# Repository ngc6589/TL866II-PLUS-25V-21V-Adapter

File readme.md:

# TL866II PLUS 25V/21V アダプター

## 概要
当アダプタは XGecu TL866II PLUS プログラマにて 2716/2732 UV-EPROM 書き込みのための 25V/21V を供給するサポートアダプターです。TL866II PLUS の書き込み電圧 18V を検出すると ROM の VPP ピンに 25V/21V を供給します。25V/21V の電圧は  9～12V の ACアダプタから供給された電圧を昇圧ICで 25V/21V にします。

基板とスライドスイッチは https://www.em9system.com/?p=965 にて頒布いたします。

## 部品表
本来は部品の種類別にソートするものですが、購入先別に分けて記載しています。

|部品番号|部品名|URL|数量|備考|
|----|----|----|----|----|
|U1|DCDCコンバーター制御用IC NJM2360AD|https://akizukidenshi.com/catalog/g/gI-12365/|1|MC34063A も使えます|
|U1|丸ピンICソケット ( 8P)|https://akizukidenshi.com/catalog/g/gP-00035/|1|
|Q1|トランジスタ 2SA733L-K-T92-K 60V150mA|https://akizukidenshi.com/catalog/g/gI-11427/|1|TO-92ECB 手持ちの 2SA1015 などもOK|
|Q2|トランジスタ 2SC945L-K-T92-K 60V150mA|https://akizukidenshi.com/catalog/g/gI-11428/|1|TO-92ECB 手持ちの 2SC1815 などもOK|
|D1,D3|ショットキーバリアダイオード 40V1A 11EQS04|https://akizukidenshi.com/catalog/g/gI-11363/|2|
|D2|定電圧ダイオード(ツェナーダイオード) 15V500mW GDZJ15C|https://akizukidenshi.com/catalog/g/gI-07498/|1|DO-34|
|C5|メタライズドポリエステルフィルムコンデンサ 1500pF100V|https://akizukidenshi.com/catalog/g/gP-14588/|1||7.5mm×6.5mm×2.5mm ピッチ5mm|
|L1|インダクター 220μH0.75A SRC1013|https://akizukidenshi.com/catalog/g/gP-16012/|1|11x12.5 ピッチ5mm|
|J1|2.1mm標準DCジャック(4A) 基板取付用 MJ-179PH|https://akizukidenshi.com/catalog/g/gC-06568/|1|
|J2|細ピンヘッダ 1×40 (黒)|https://akizukidenshi.com/catalog/g/gC-06631/|1|
|J3|ゼロプレッシャーICソケット 24P 600mil|https://akizukidenshi.com/catalog/g/gP-12077/|1|
|JP1|ジャンパーピン赤(2.54mmピッチ)(25個入)|https://akizukidenshi.com/catalog/g/gP-03688/|1|
|R1|小形金属皮膜抵抗(MOSX)2W 0.22Ω【MOSX2CR22J】 |https://www.marutsu.co.jp/pc/i/18085/|1|L=15mm D=4mm|
|R2|【MOS2C181J】小型酸金抵抗(MOS)2W 180Ω|https://www.marutsu.co.jp/pc/i/18155/|1|L=15mm D=4mm|
|R3|1/4W金属皮膜抵抗 4.7kΩ 黄紫黒茶茶【MF1/4CC4701F】 |https://www.marutsu.co.jp/pc/i/1313/|1|L=7.1mm D=2.3mm|
|R4|1/4W金属皮膜抵抗 24kΩ 赤黄黒赤茶【MF1/4CC2402F】 |https://www.marutsu.co.jp/pc/i/1283/|1|L=7.1mm D=2.3mm|
|R5|1/4W金属皮膜抵抗 1.5kΩ 茶緑黒茶茶【MF1/4CC1501F】|https://www.marutsu.co.jp/pc/i/1248/|1|L=7.1mm D=2.3mm|
|R6,R8,R9|1/4W金属皮膜抵抗 1kΩ 茶黒黒茶茶【MF1/4CC1001F】|https://www.marutsu.co.jp/pc/i/1263/|3|L=7.1mm D=2.3mm|
|R7|1/4W金属皮膜抵抗 12kΩ 茶赤黒赤茶【MF1/4CC1202F】|https://www.marutsu.co.jp/pc/i/1253/|1|L=7.1mm D=2.3mm|
|R10|1/4W金属皮膜抵抗 10kΩ 茶黒黒赤茶【MF1/4CC1002F】|https://www.marutsu.co.jp/pc/i/1251/|1|L=7.1mm D=2.3mm|
|C1,C3|【RDER71H104K0K1H03B】セラミックコンデンサ 0.1UF 50V X7R ラジアル|https://www.marutsu.co.jp/pc/i/834991/|2|4mmx2.5mm ピッチ5mm|
|C2|小形アルミニウム電解コンデンサー25V 100μF【25PK100MEFC】|https://www.marutsu.co.jp/pc/i/132144/|1|D=5mm ピッチ2mm|
|C4|小形アルミニウム電解コンデンサー50V 330μF【50PK330MEFC】|https://www.marutsu.co.jp/pc/i/132162/|1|D=10 ピッチ5mm|
|JP1|2ピン基板用ピンヘッダー[2ピン×1列]【2130S1*2GSE】 |https://www.marutsu.co.jp/pc/i/590531/|1|
||SSSF040800 ALPS ALPINE スライドスイッチ|https://www.chip1stop.com/product/detail?partId=ALPS-0000163|1|4PDT スライドスイッチ 頒布品を買われた方は購入不要|
||プリント基板||1|頒布品を買われた方は基板製造不要|

- R1, R2 は 2W サイズと大きいものを選定していますが、ROM のプログラミングだけでこのワット数は不要です。しかしながらこの回路を参考にされて電流を取り出す用途に流用された時は、発熱の可能性があるためマージンを取った形にしています。
- Q1, Q2 汎用でいいのですが、秋月だと10個単位とかになってしまうので1個単位で買えるトランジスタを選定しています。
- 1/4W 抵抗のうち、R3, R4, R5 は DC/DC チップの基準電圧用なので金属皮膜 1% を使用して下さい。それ以外の抵抗は 5% カーボンでも問題ありません。これも通販だと 10本/100本単位がほとんどなので1本単位で購入出来るものにしています。

部品表には書いていませんが、9～12V の ACアダプタもご用意ください。

## 回路図
リポジトリにある schematic-nnnnnn.pdf (nnnnnnは日付) を参照下さい。

## ガーバーファイル
リポジトリにある gaeber-nnnnnn.zip (nnnnnnは日付) を参照下さい。

## 組み立て時の注意
**ZIF ソケットをハンダ付けする前に細ピンヘッダを先にハンダ付けしてください。** これ以外は特に取り付け順はありません。

下の写真は、別バージョンの基板ですが、ZIF ソケットに隠れる細ピンヘッダを先に半田付けしているところ。

## 書き込み実績
手持ちが少ないですが以下の ROM 書き込み出来ました。
- NEC D2716D(25V)
- MITSUBISHI M5L2716K(25V)
- FUJITSU MB8516(25V)
- FUJITSU MBM2732A(21V)
- INTEL D2732A-3(21V)
- TOSHIBA TMM2732D(25V)
- MITSUBISHI M5L2732K(25V)
- HITACHI HN482732AG(21V)

## 書き込み方法
- アダプタを TL866II PLUS のソケットに装着する
- ROM の書き込み電圧に合わせて 25V はジャンパを外す 21V ならジャンパ装着する
- スライドスイッチを 2716/2732 に合わせる
- 9～12V の ACアダプタを当基板に挿して電源供給する。
- XGpro アプリケーションを起動しチップの選択をします。
- 画面左下の [Pin Detect] のチェックボックスを外す

- READ ボタンを押してエラーないことを確認
- HEX ファイルを LOAD する
- WRITE ボタンを押して書き込む
- 書き込み不調の場合は Pulse Delay を最大 1000us にするといけることがあります。

## 2732 書き込み時の注意点

2732 の書き込みは XGpro v11.90 のバージョンではエラーになります。次の写真のように 2732 18Pin CE（チップイネーブル）を 12pPin GND にジャンパして強制的に CE 有効にして書き込みを行ってください。これはアプリケーションの不具合で現状これ以外のワークアラウンドは無い模様です。

## ~~rel 2022/04/13 基板作成時の変更点~~
~~初版の基板にはエラーがあります。R3 3.6k のシルク間違いと半固定抵抗の配線ミスと GND 配線忘れです。~~
- ~~R3 はシルク印刷 3.6k ですが実装は 4.7k です。~~
- ~~半固定抵抗は抵抗の余りリード線を使ってショートします~~
- ~~ZIF ソケットの 12 ピンと GND を抵抗の余りリード線を使ってショートします~~

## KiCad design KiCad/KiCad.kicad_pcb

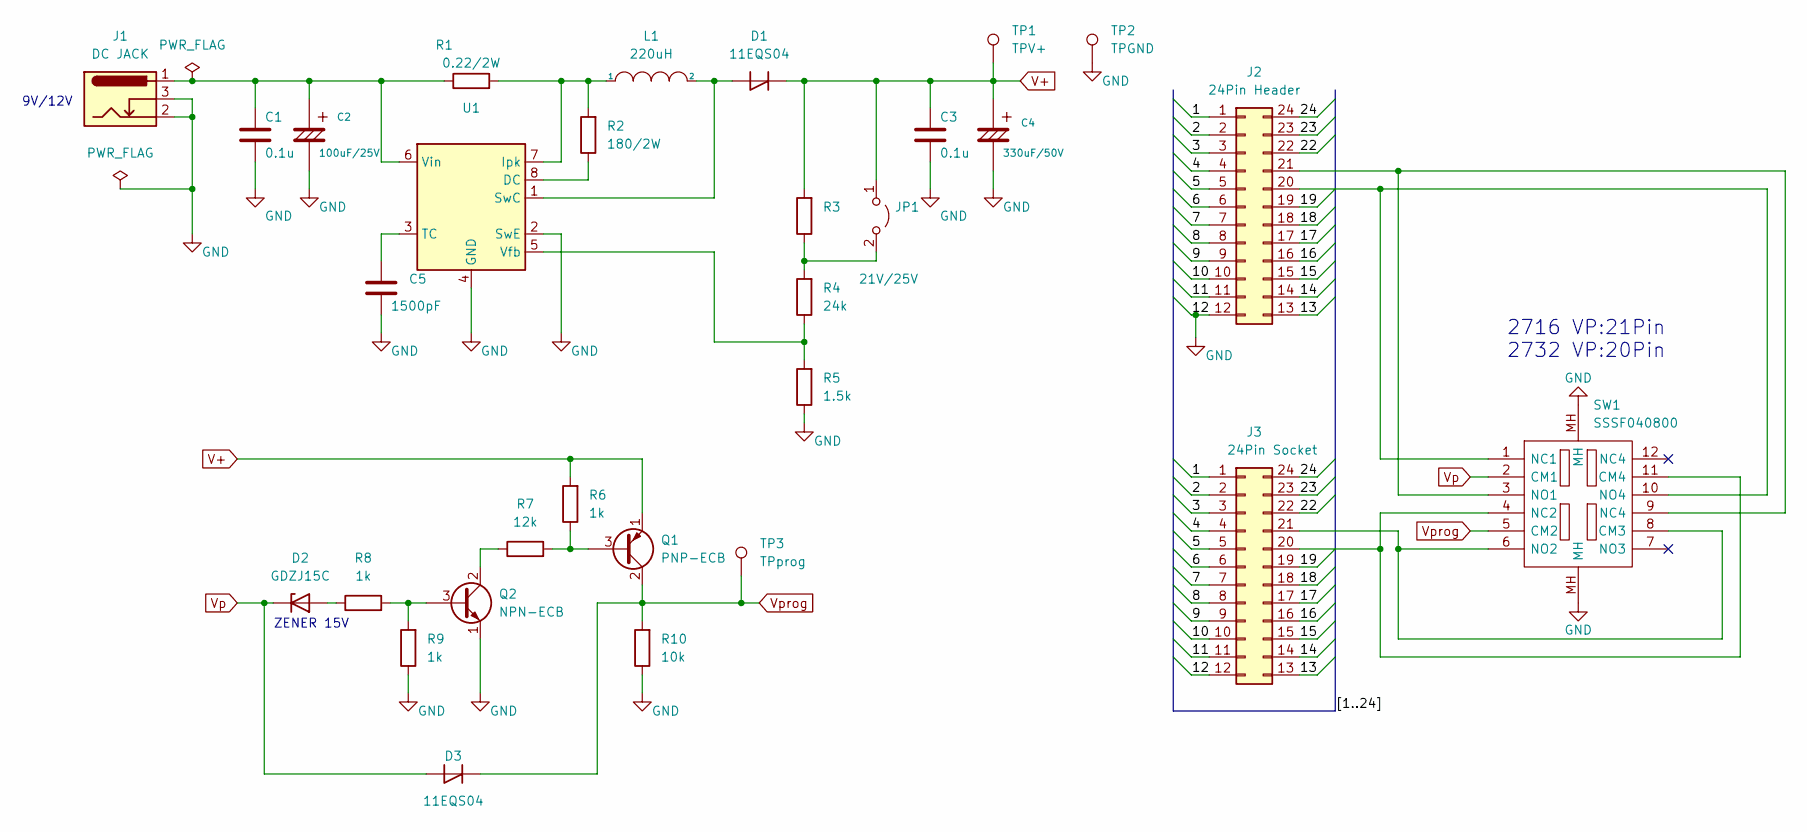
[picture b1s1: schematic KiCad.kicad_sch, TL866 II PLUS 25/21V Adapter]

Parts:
C1, C3: 0.1u; C_Disc_D4.7mm_W2.5mm_P5.00mm
C2: 100uF/25V; CP_Radial_D5.0mm_P2.00mm
C4: 330uF/50V; CP_Radial_D10.0mm_P5.00mm
C5: 1500pF; C_Rect_L7.2mm_W2.5mm_P5.00mm_FKS2_FKP2_MKS2_MKP2
D1, D3: 11EQS04; D_DO-41_SOD81_P10.16mm_Horizontal
D2: GDZJ15C; D_DO-34_SOD68_P7.62mm_Horizontal
J1: DC JACK; MJ-179PH
J2: 24Pin Header; DIP-24_W7.62mm
J3: 24Pin Socket; DIP_Socket-24_W11.9_W12.7_W15.24_W17.78_W18.5_3M_224-1275-0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
JP1: 21V/25V; PinHeader_1x02_P2.54mm_Vertical
L1: 220uH; L_Radial_D12.0mm_P5.00mm_Fastron_11P
Q1: PNP-ECB; TO-92
Q2: NPN-ECB; TO-92
R1: 0.22/2W; R_Axial_DIN0414_L11.9mm_D4.5mm_P15.24mm_Horizontal
R2: 180/2W; R_Axial_DIN0414_L11.9mm_D4.5mm_P15.24mm_Horizontal
R3: R_Axial_DIN0207_L6.3mm_D2.5mm_P7.62mm_Horizontal
R4: 24k; R_Axial_DIN0207_L6.3mm_D2.5mm_P7.62mm_Horizontal
R5: 1.5k; R_Axial_DIN0207_L6.3mm_D2.5mm_P7.62mm_Horizontal
R6, R8, R9: 1k; R_Axial_DIN0207_L6.3mm_D2.5mm_P7.62mm_Horizontal
R7: 12k; R_Axial_DIN0207_L6.3mm_D2.5mm_P7.62mm_Horizontal
R10: 10k; R_Axial_DIN0207_L6.3mm_D2.5mm_P7.62mm_Horizontal
SW1: SSSF040800
TP1: TPV+; TestPoint_THTPad_D2.0mm_Drill1.0mm
TP2: TPGND; TestPoint_THTPad_D2.0mm_Drill1.0mm
TP3: TPprog; TestPoint_THTPad_D2.0mm_Drill1.0mm
U1: DIP-8_W7.62mm

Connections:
/1: J2.1, J3.1
/2: J2.2, J3.2
/3: J2.3, J3.3
/4: J2.4, J3.4
/5: J2.5, J3.5
/6: J2.6, J3.6
/7: J2.7, J3.7
/8: J2.8, J3.8
/9: J2.9, J3.9
/10: J2.10, J3.10
/11: J2.11, J3.11
/13: J2.13, J3.13
/14: J2.14, J3.14
/15: J2.15, J3.15
/16: J2.16, J3.16
/17: J2.17, J3.17
/18: J2.18, J3.18
/19: J2.19, J3.19
/22: J2.22, J3.22
/23: J2.23, J3.23
/24: J2.24, J3.24
GND: C1.2, C2.2, C3.2, C4.2, C5.2, J1.2, J1.3, J2.12, J3.12, Q2.1 (E), R5.1, R9.1, R10.1, SW1.MH, TP2.1, U1.2 (SwE), U1.4 (GND)
unnamed: C1.1, C2.1, J1.1, R1.1, U1.6 (Vin)
unnamed: C5.1, U1.3 (TC)
unnamed: D1.2 (A), L1.2, U1.1 (SwC)
unnamed: D2.2 (A), R8.1
unnamed: J2.20, SW1.1 (NC1), SW1.10 (NO4)
unnamed: J2.21, SW1.3 (NO1), SW1.9 (NC4)
unnamed: J3.20, SW1.4 (NC2), SW1.11 (CM4)
unnamed: J3.21, SW1.6 (NO2), SW1.8 (CM3)
unnamed: JP1.2 (B), R3.1, R4.2
unnamed: L1.1, R1.2, R2.2, U1.7 (Ipk)
unnamed: Q1.3 (B), R6.1, R7.2
unnamed: Q2.2 (C), R7.1
unnamed: Q2.3 (B), R8.2, R9.2
unnamed: R2.1, U1.8 (DC)
unnamed: R4.1, R5.2, U1.5 (Vfb)
V+: C3.1, C4.1, D1.1 (K), JP1.1 (A), Q1.1 (E), R3.2, R6.2, TP1.1
Vp: D2.1 (K), D3.2 (A), SW1.2 (CM1)
Vprog: D3.1 (K), Q1.2 (C), R10.2, SW1.5 (CM2), TP3.1

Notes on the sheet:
ZENER 15V
2716 VP:21Pin 2732 VP:20Pin
9V/12V

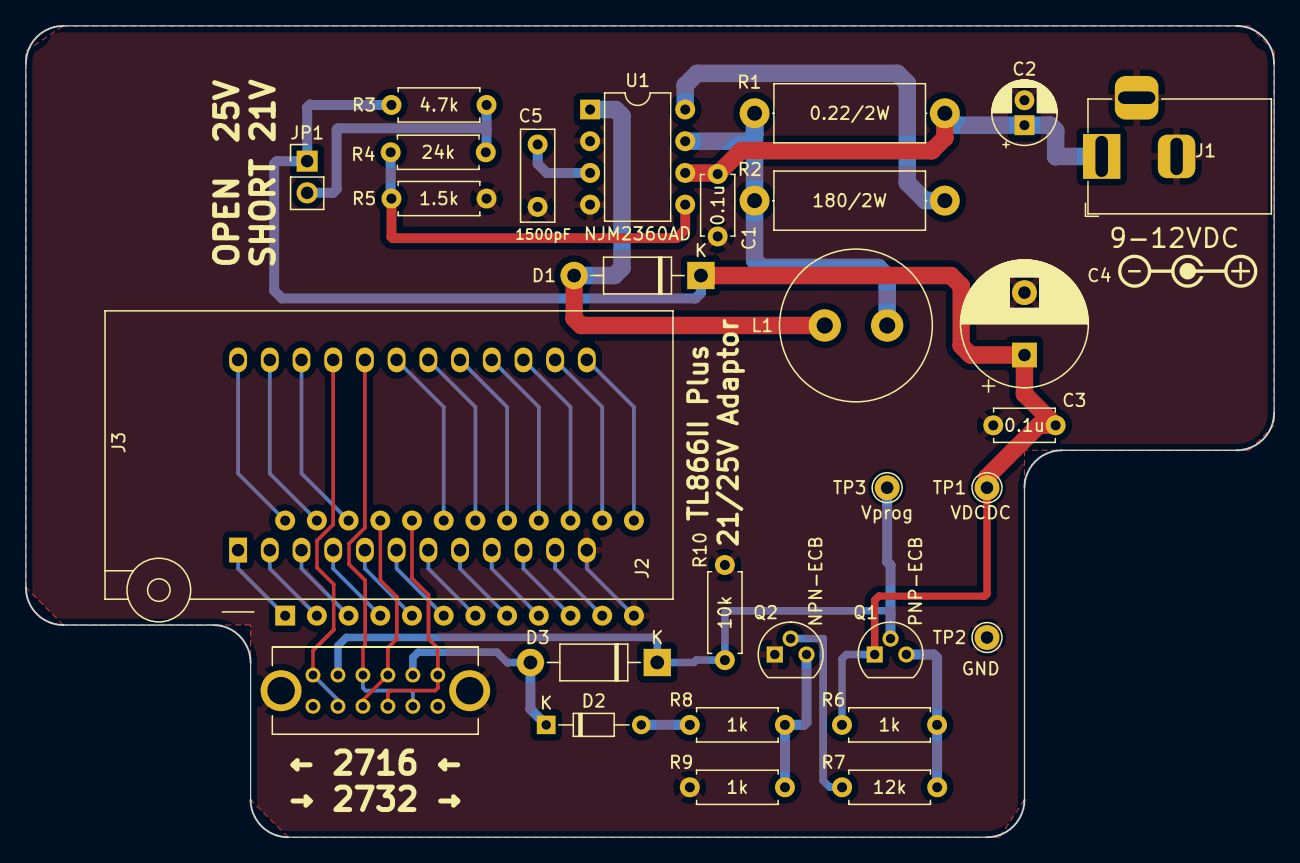
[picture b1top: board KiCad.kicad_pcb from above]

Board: 2 copper layers, 100.0 x 65.0 mm, 30 parts (0 on the bottom side), 40 nets.

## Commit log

2022-04-21 add readme.md
2022-04-21 add schematic.pdf
2022-04-21 add photos
2022-04-21 move photos
2022-04-21 add KiCad and some files
2022-04-21 add screenshot
2022-05-07 add photo3
2022-06-20 modify readme.md
2022-06-20 add .gitignore
2022-06-20 mod .gitignore
2022-06-20 remove kicad backup files
2023-03-19 Q1 PNP トランジスタの商品ページ URL を更新
